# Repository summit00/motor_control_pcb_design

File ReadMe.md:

# STM32H563 BLDC Motor Controller

A three-phase BLDC/PMSM motor controller designed for high-performance Field-Oriented Control (FOC).

## Features

- STM32H563 microcontroller
- DRV8353 three-phase gate driver
- Three low-side current shunts
- Up to 60 V DC bus
- CAN interface
- USB-C interface
- Incremental encoder interface

## Repository Structure

```
.
├── motor_bldc_esc_V1.kicad_pro
├── motor_bldc_esc_V1.kicad_sch
├── motor_bldc_esc_V1.kicad_pcb
├── powerstage.kicad_sch
├── power.kicad_sch
├── mcu.kicad_sch
├── communication.kicad_sch
└── encoder.kicad_sch
```

## Status

🚧 Work in progress.

The hardware is currently under development and has not yet been validated on physical hardware.

## License

Hardware released under the CERN Open Hardware License.

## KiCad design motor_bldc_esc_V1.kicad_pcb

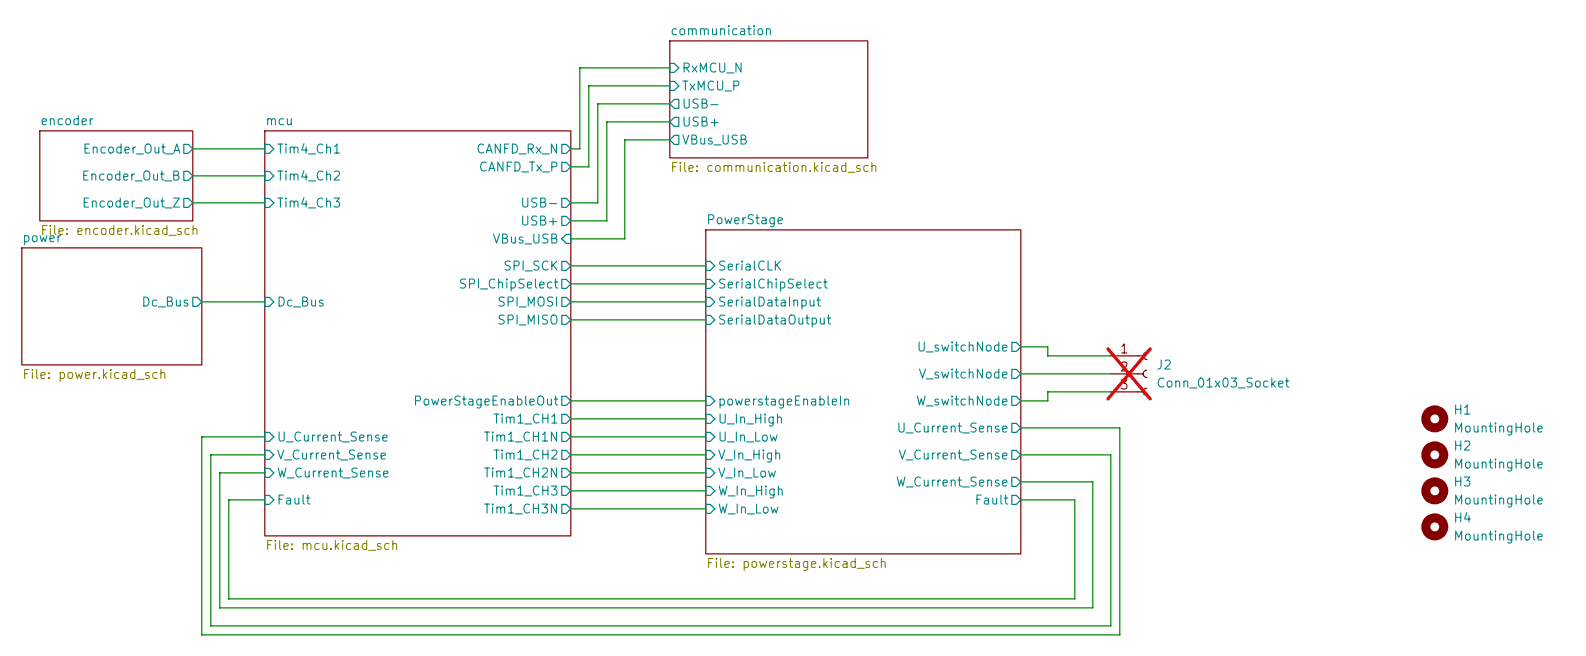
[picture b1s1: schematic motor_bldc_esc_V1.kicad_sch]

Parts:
H1, H2, H3, H4: MountingHole; MountingHole_3.2mm_M3
J2: Conn_01x03_Socket; SolderWire-4sqmm_1x03_P12mm_D3mm_OD6mm; not fitted

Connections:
/PowerStage/U_switchNode: J2.1; also elsewhere on the board
/PowerStage/V_switchNode: J2.2; also elsewhere on the board
/PowerStage/W_switchNode: J2.3; also elsewhere on the board

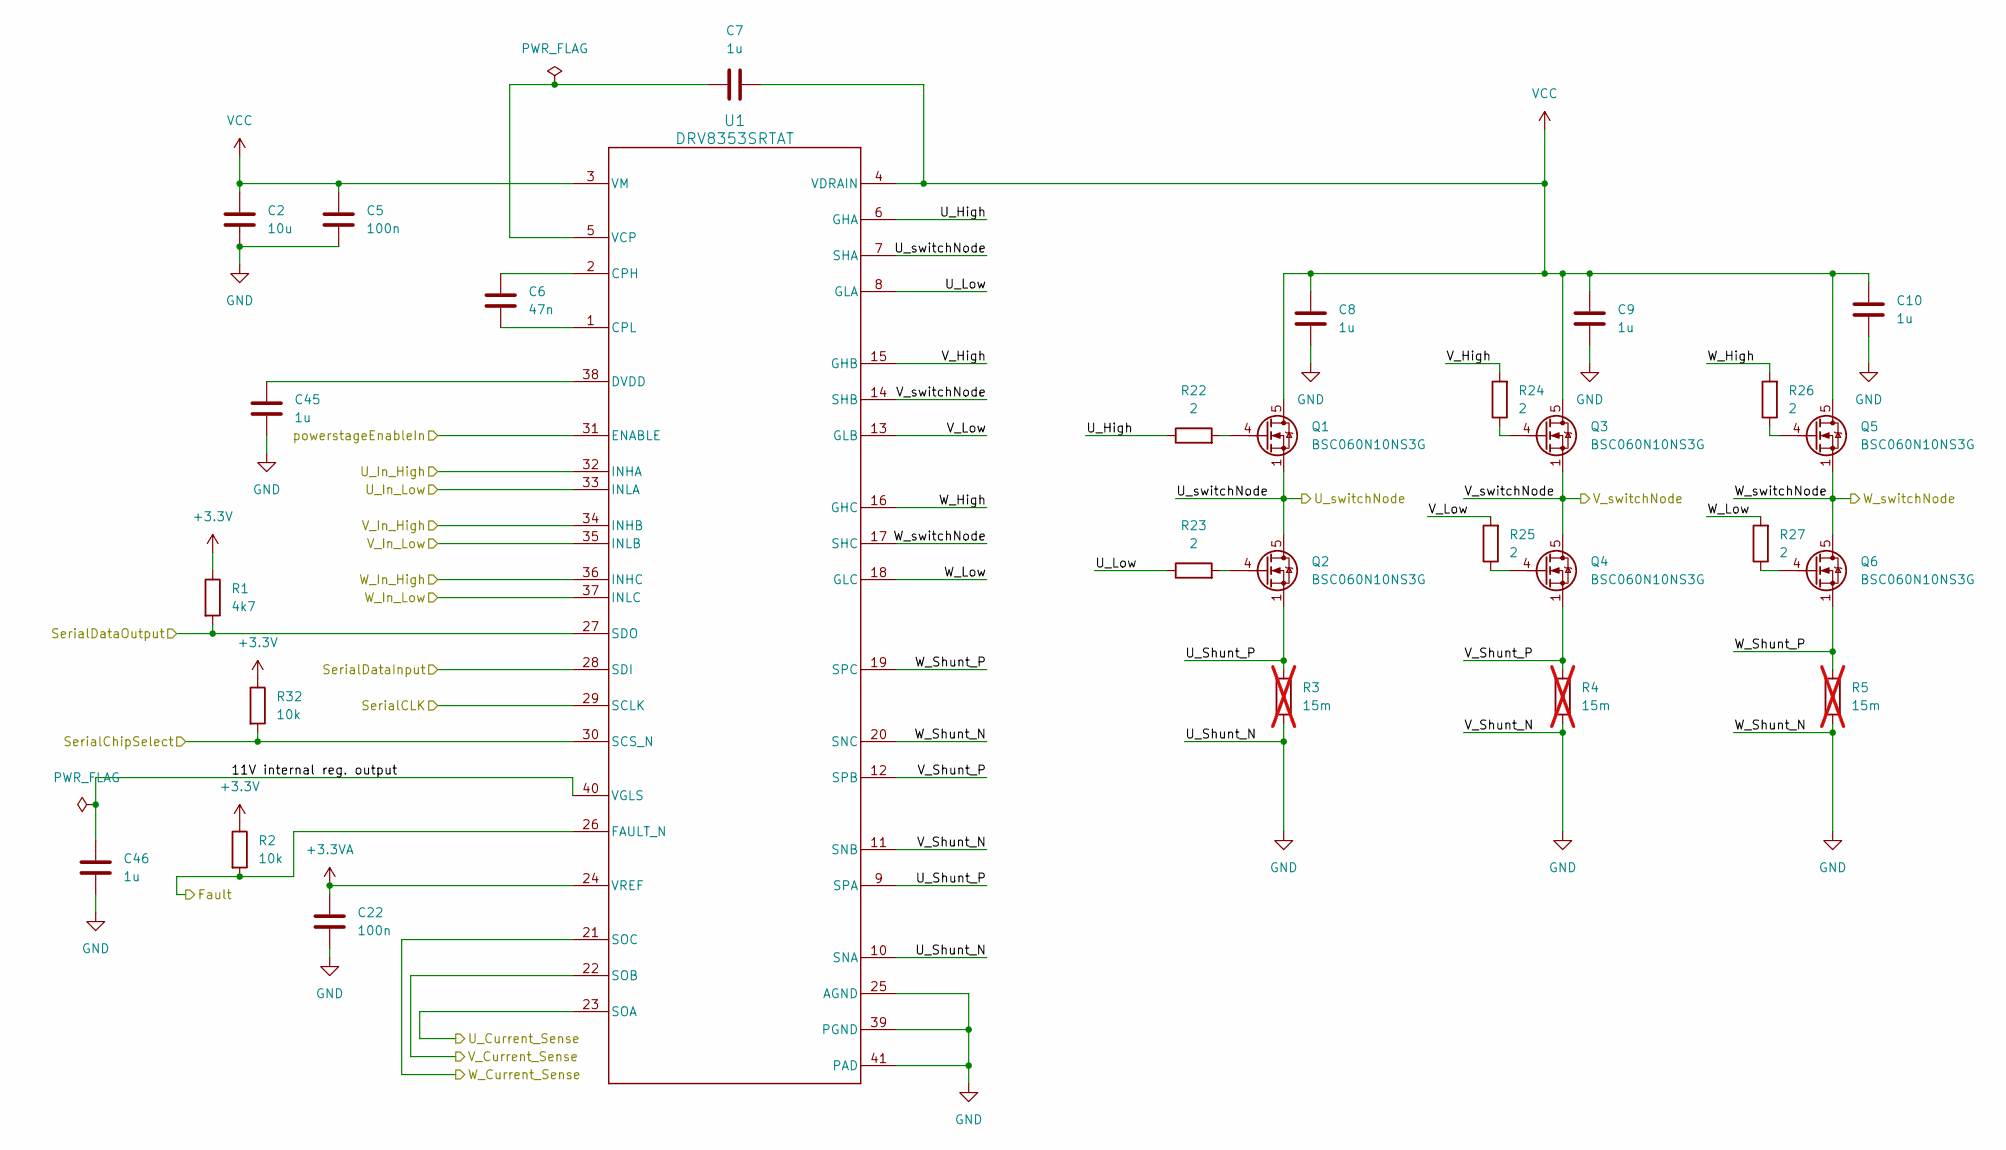
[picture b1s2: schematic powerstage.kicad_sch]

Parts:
C2: 10u; C_1210_3225Metric_Pad1.33x2.70mm_HandSolder; LCSC C5156756
C5: 100n; C_0805_2012Metric_Pad1.18x1.45mm_HandSolder; LCSC Part # C28233
C6: 47n; C_0805_2012Metric_Pad1.18x1.45mm_HandSolder; LCSC Part # C53134
C7: 1u; C_0805_2012Metric_Pad1.18x1.45mm_HandSolder; LCSC Part # C28323
C8, C9, C10: 1u; C_0805_2012Metric_Pad1.18x1.45mm_HandSolder; LCSC Part # C5370002
C22: 100n; C_0603_1608Metric; LCSC Part # C14663
C45, C46: 1u; C_0603_1608Metric; LCSC Part # C15849
Q1, Q2, Q3, Q4, Q5, Q6: BSC060N10NS3G; TDSON-8-1; LCSC Part # C501504
R1: 4k7; R_0603_1608Metric; LCSC Part # C23162
R2, R32: 10k; R_0805_2012Metric_Pad1.20x1.40mm_HandSolder; LCSC Part # C17414
R3, R4, R5: 15m; R_2512_6332Metric_Pad1.40x3.35mm_HandSolder; LCSC C7420045; not fitted
R22, R23, R24, R25, R26, R27: 2; R_0603_1608Metric; LCSC Part # C22977
U1: DRV8353SRTAT; LCSC Part # C2150480

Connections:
+3.3V: R1.1, R2.1, R32.1; also elsewhere on the board
+3.3VA: C22.1, U1.24 (VREF); also elsewhere on the board
/PowerStage/11V internal reg. output: C46.1, U1.40 (VGLS)
/PowerStage/Fault: R2.2, U1.26 (FAULT_N); also elsewhere on the board
/PowerStage/SerialCLK: U1.29 (SCLK); also elsewhere on the board
/PowerStage/SerialChipSelect: R32.2, U1.30 (SCS_N); also elsewhere on the board
/PowerStage/SerialDataInput: U1.28 (SDI); also elsewhere on the board
/PowerStage/SerialDataOutput: R1.2, U1.27 (SDO); also elsewhere on the board
/PowerStage/U_Current_Sense: U1.23 (SOA); also elsewhere on the board
/PowerStage/U_High: R22.1, U1.6 (GHA)
/PowerStage/U_In_High: U1.32 (INHA); also elsewhere on the board
/PowerStage/U_In_Low: U1.33 (INLA); also elsewhere on the board
/PowerStage/U_Low: R23.1, U1.8 (GLA)
/PowerStage/U_Shunt_P: Q2.1 (S), Q2.2 (S), Q2.3 (S), R3.1, U1.9 (SPA)
/PowerStage/U_switchNode: Q1.1 (S), Q1.2 (S), Q1.3 (S), Q2.5 (D), U1.7 (SHA); also elsewhere on the board
/PowerStage/V_Current_Sense: U1.22 (SOB); also elsewhere on the board
/PowerStage/V_High: R24.2, U1.15 (GHB)
/PowerStage/V_In_High: U1.34 (INHB); also elsewhere on the board
/PowerStage/V_In_Low: U1.35 (INLB); also elsewhere on the board
/PowerStage/V_Low: R25.2, U1.13 (GLB)
/PowerStage/V_Shunt_P: Q4.1 (S), Q4.2 (S), Q4.3 (S), R4.1, U1.12 (SPB)
/PowerStage/V_switchNode: Q3.1 (S), Q3.2 (S), Q3.3 (S), Q4.5 (D), U1.14 (SHB); also elsewhere on the board
/PowerStage/W_Current_Sense: U1.21 (SOC); also elsewhere on the board
/PowerStage/W_High: R26.2, U1.16 (GHC)
/PowerStage/W_In_High: U1.36 (INHC); also elsewhere on the board
/PowerStage/W_In_Low: U1.37 (INLC); also elsewhere on the board
/PowerStage/W_Low: R27.2, U1.18 (GLC)
/PowerStage/W_Shunt_P: Q6.1 (S), Q6.2 (S), Q6.3 (S), R5.1, U1.19 (SPC)
/PowerStage/W_switchNode: Q5.1 (S), Q5.2 (S), Q5.3 (S), Q6.5 (D), U1.17 (SHC); also elsewhere on the board
/PowerStage/powerstageEnableIn: U1.31 (ENABLE); also elsewhere on the board
GND: C2.2, C5.1, C8.2, C9.2, C10.2, C22.2, C45.2, C46.2, R3.2, R4.2, R5.2, U1.10 (SNA), U1.11 (SNB), U1.20 (SNC), U1.25 (AGND), U1.39 (PGND), U1.41 (PAD); also elsewhere on the board
unnamed: Q1.4 (G), R22.2
unnamed: Q2.4 (G), R23.2
unnamed: Q3.4 (G), R24.1
unnamed: Q4.4 (G), R25.1
unnamed: Q5.4 (G), R26.1
unnamed: Q6.4 (G), R27.1
unnamed: C6.2, U1.2 (CPH)
unnamed: C6.1, U1.1 (CPL)
unnamed: C45.1, U1.38 (DVDD)
unnamed: C7.1, U1.5 (VCP)
VCC: C2.1, C5.2, C7.2, C8.1, C9.1, C10.1, Q1.5 (D), Q3.5 (D), Q5.5 (D), U1.3 (VM), U1.4 (VDRAIN); also elsewhere on the board

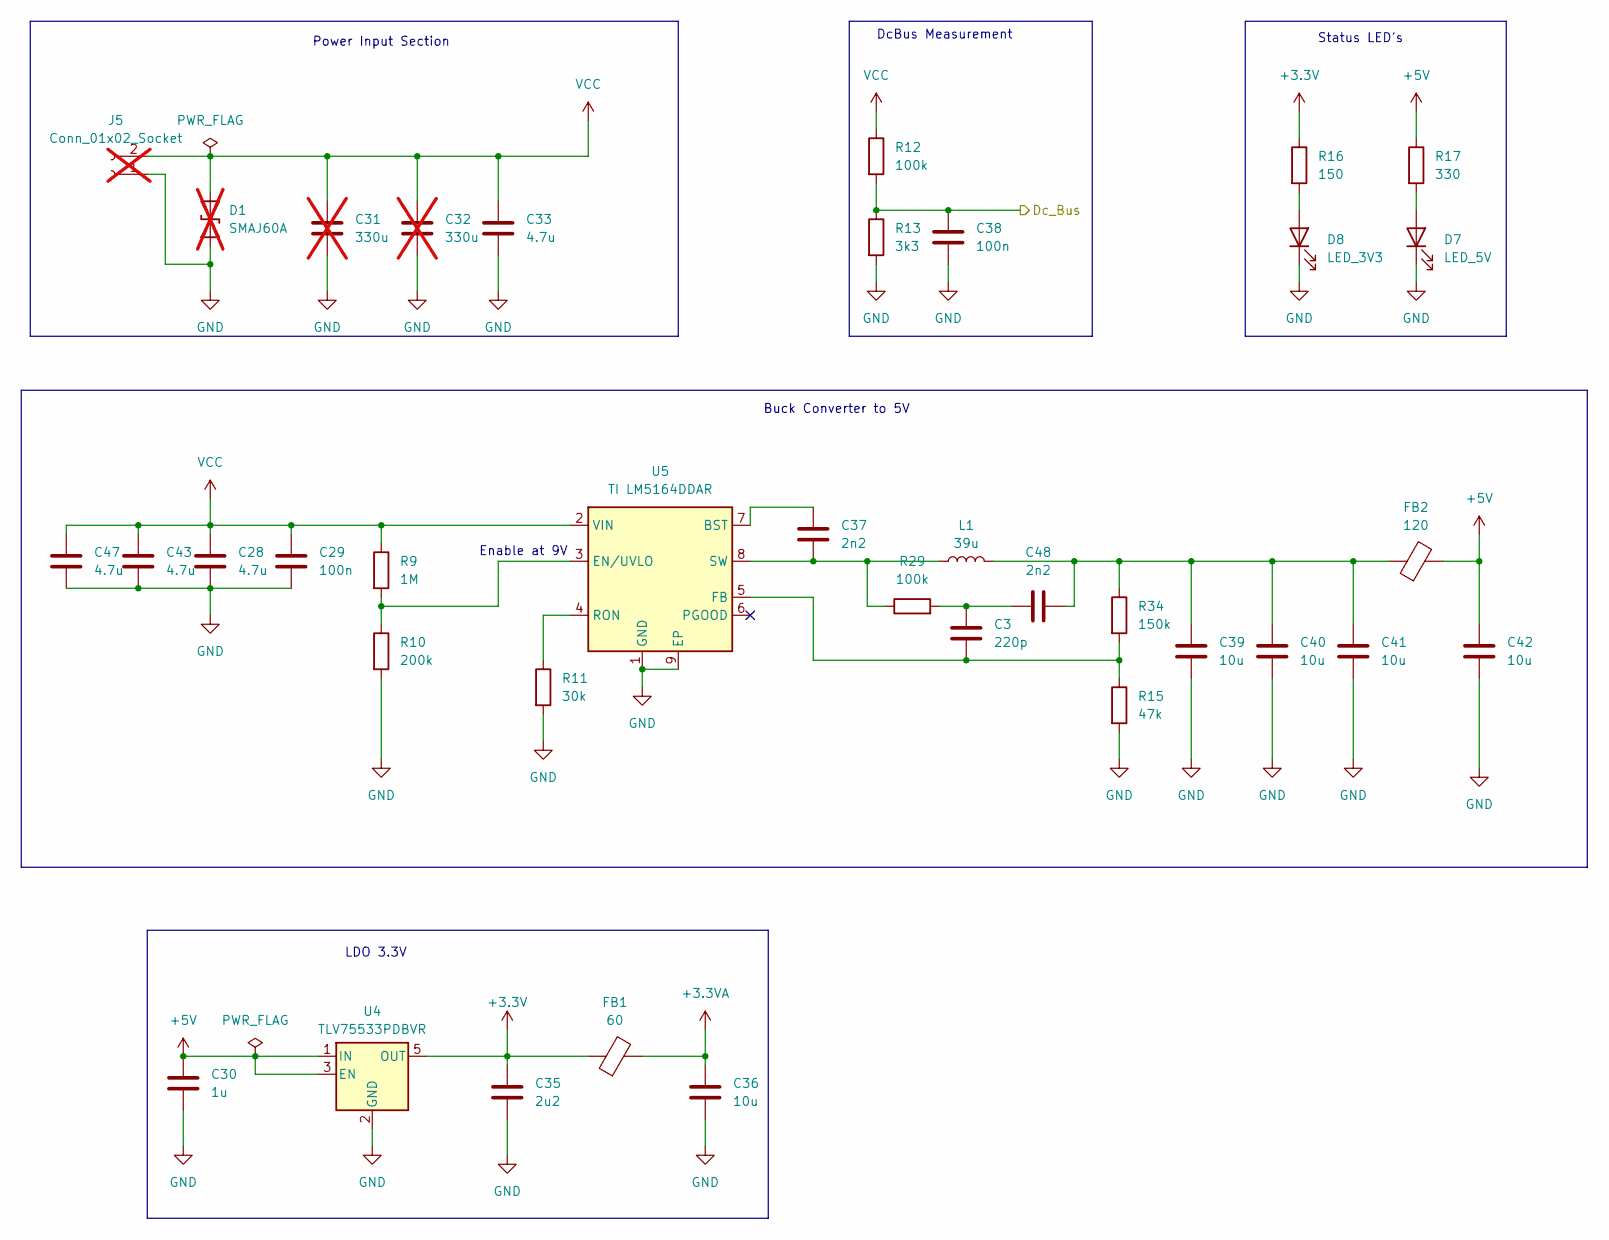
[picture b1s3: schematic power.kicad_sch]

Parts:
C3: 220p; C_0603_1608Metric; LCSC Part # C1603
C28, C33, C43, C47: 4.7u; C_1210_3225Metric_Pad1.33x2.70mm_HandSolder; LCSC C381466
C29, C38: 100n; C_0805_2012Metric_Pad1.18x1.45mm_HandSolder; LCSC Part # C28233
C30: 1u; C_0603_1608Metric; LCSC Part # C15849
C31, C32: 330u; 100ZLJ330M12.5X35; not fitted
C35: 2u2; C_0603_1608Metric; LCSC Part # C23630
C36, C39, C40, C41, C42: 10u; R_0805_2012Metric_Pad1.20x1.40mm_HandSolder; LCSC Part # C15850
C37, C48: 2n2; C_0603_1608Metric; LCSC Part # C1604
D1: SMAJ60A; D_SMA-SMB_Universal_Handsoldering; not fitted
D7: LED_5V; LED_0805_2012Metric; LCSC C84256
D8: LED_3V3; LED_0805_2012Metric; LCSC C84256
FB1: 60; L_0805_2012Metric_Pad1.05x1.20mm_HandSolder; LCSC Part # C845118
FB2: 120; L_0603_1608Metric_Pad1.05x0.95mm_HandSolder; LCSC Part # C14709
J5: Conn_01x02_Socket; SolderWire-4sqmm_1x02_P12mm_D3mm_OD6mm; not fitted
L1: 39u; L_Sunlord_SWPA8040S; LCSC Part # C206289
R9: 1M; R_0805_2012Metric; LCSC Part # C17514
R10: 200k; R_0805_2012Metric; LCSC Part # C17539
R11: 30k; R_0603_1608Metric; LCSC C22984
R12: 100k; R_0805_2012Metric_Pad1.20x1.40mm_HandSolder; LCSC Part # C149504
R13: 3k3; R_0805_2012Metric_Pad1.20x1.40mm_HandSolder; LCSC Part # C26010
R15: 47k; R_0603_1608Metric; LCSC Part # C25819
R16: 150; R_0805_2012Metric_Pad1.20x1.40mm_HandSolder; LCSC Part # C17471
R17: 330; R_0603_1608Metric; LCSC Part # C23138
R29: 100k; R_0603_1608Metric; LCSC Part # C25803
R34: 150k; R_0603_1608Metric; LCSC Part # C22807
U4: TLV75533PDBVR; SOT-23-5; LCSC Part # C404027
U5: TI LM5164DDAR; LM5164DDAR; LCSC Part # C477928

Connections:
+3.3V: C35.1, FB1.1, R16.1, U4.5 (OUT); also elsewhere on the board
+3.3VA: C36.1, FB1.2; also elsewhere on the board
+5V: C30.1, C42.1, FB2.2, R17.1, U4.1 (IN), U4.3 (EN); also elsewhere on the board
/mcu/Dc_Bus: C38.2, R12.2, R13.1; also elsewhere on the board
GND: C28.2, C29.1, C30.2, C31.2, C32.2, C33.2, C35.2, C36.2, C38.1, C39.2, C40.2, C41.2, C42.2, C43.2, C47.2, D1.1 (A1), D7.1 (K), D8.1 (K), J5.1, R10.2, R11.2, R13.2, R15.2, U4.2 (GND), U5.1 (GND), U5.9 (EP); also elsewhere on the board
unnamed: C3.1, C48.1, R29.2
unnamed: C39.1, C40.1, C41.1, C48.2, FB2.1, L1.2, R34.1
unnamed: D7.2 (A), R17.2
unnamed: D8.2 (A), R16.2
unnamed: C37.1, U5.7 (BST)
unnamed: R9.2, R10.1, U5.3 (EN/UVLO)
unnamed: C3.2, R15.1, R34.2, U5.5 (FB)
unnamed: R11.1, U5.4 (RON)
unnamed: C37.2, L1.1, R29.1, U5.8 (SW)
VCC: C28.1, C29.2, C31.1, C32.1, C33.1, C43.1, C47.1, D1.2 (A2), J5.2, R9.1, R12.1, U5.2 (VIN); also elsewhere on the board

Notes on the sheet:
Buck Converter to 5V
Enable at 9V
Power Input Section
LDO 3.3V
Status LED's
DcBus Measurement

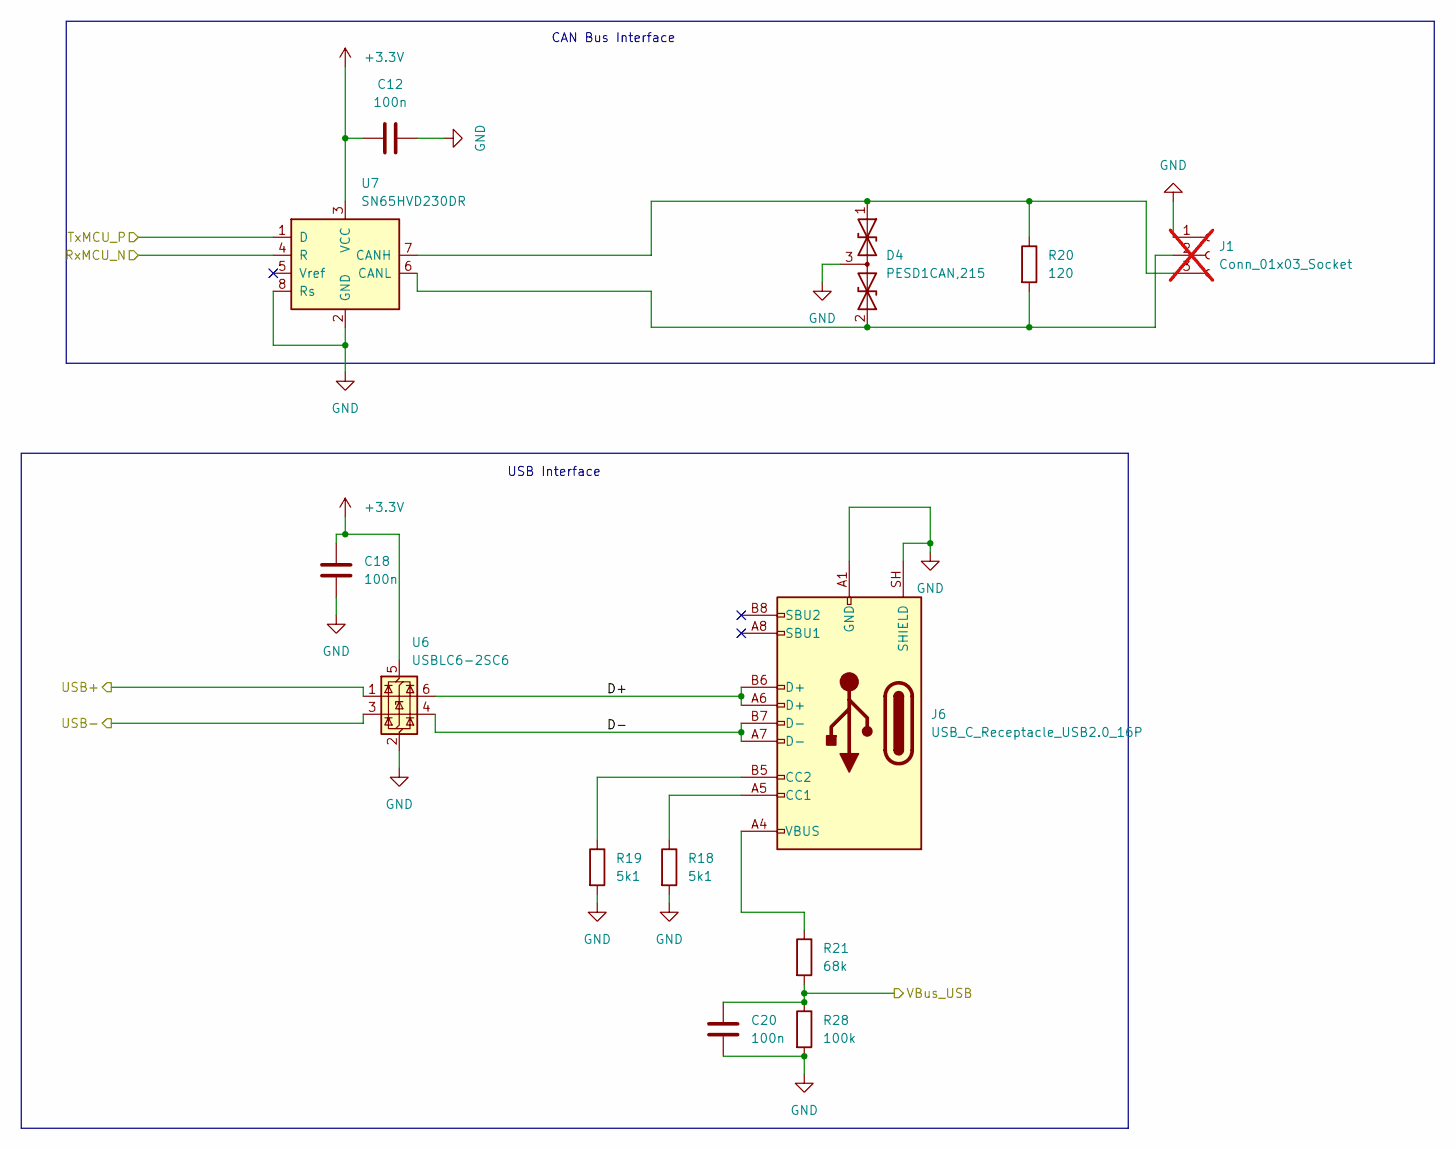
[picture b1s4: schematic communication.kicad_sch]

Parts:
C12, C18, C20: 100n; C_0603_1608Metric; LCSC Part # C14663
D4: PESD1CAN,215; SOT-23; LCSC Part # C15771
J1: Conn_01x03_Socket; JST_EH_B3B-EH-A_1x03_P2.50mm_Vertical; not fitted
J6: USB_C_Receptacle_USB2.0_16P; USB_C_Receptacle_G-Switch_GT-USB-7010ASV; LCSC Part # C2988369
R18, R19: 5k1; R_0603_1608Metric; LCSC Part # C23189
R20: 120; R_0603_1608Metric; LCSC Part # C22787
R21: 68k; R_0603_1608Metric; LCSC Part # C23231
R28: 100k; R_0603_1608Metric; LCSC Part # C25803
U6: USBLC6-2SC6; SOT-23-6; LCSC Part # C7519
U7: SN65HVD230DR; SOIC-8_3.9x4.9mm_P1.27mm; LCSC Part # C12084

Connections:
+3.3V: C12.1, C18.1, U6.5 (VBUS), U7.3 (VCC); also elsewhere on the board
/communication/D+: J6.A6 (D+), J6.B6 (D+), U6.6 (I/O1)
/communication/D-: J6.A7 (D-), J6.B7 (D-), U6.4 (I/O2)
/communication/RxMCU_N: U7.4 (R); also elsewhere on the board
/communication/TxMCU_P: U7.1 (D); also elsewhere on the board
/communication/USB+: U6.1 (I/O1); also elsewhere on the board
/communication/USB-: U6.3 (I/O2); also elsewhere on the board
/communication/VBus_USB: C20.1, R21.2, R28.1; also elsewhere on the board
GND: C12.2, C18.2, C20.2, D4.3 (common), J1.1, J6.A1 (GND), J6.A12 (GND), J6.B1 (GND), J6.B12 (GND), J6.SH (SHIELD), R18.2, R19.2, R28.2, U6.2 (GND), U7.2 (GND), U7.8 (Rs); also elsewhere on the board
unnamed: D4.1 (A1), J1.3, R20.1, U7.7 (CANH)
unnamed: D4.2 (A2), J1.2, R20.2, U7.6 (CANL)
unnamed: J6.A5 (CC1), R18.1
unnamed: J6.B5 (CC2), R19.1
unnamed: J6.A4 (VBUS), J6.A9 (VBUS), J6.B4 (VBUS), J6.B9 (VBUS), R21.1

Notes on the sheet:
CAN Bus Interface
USB Interface

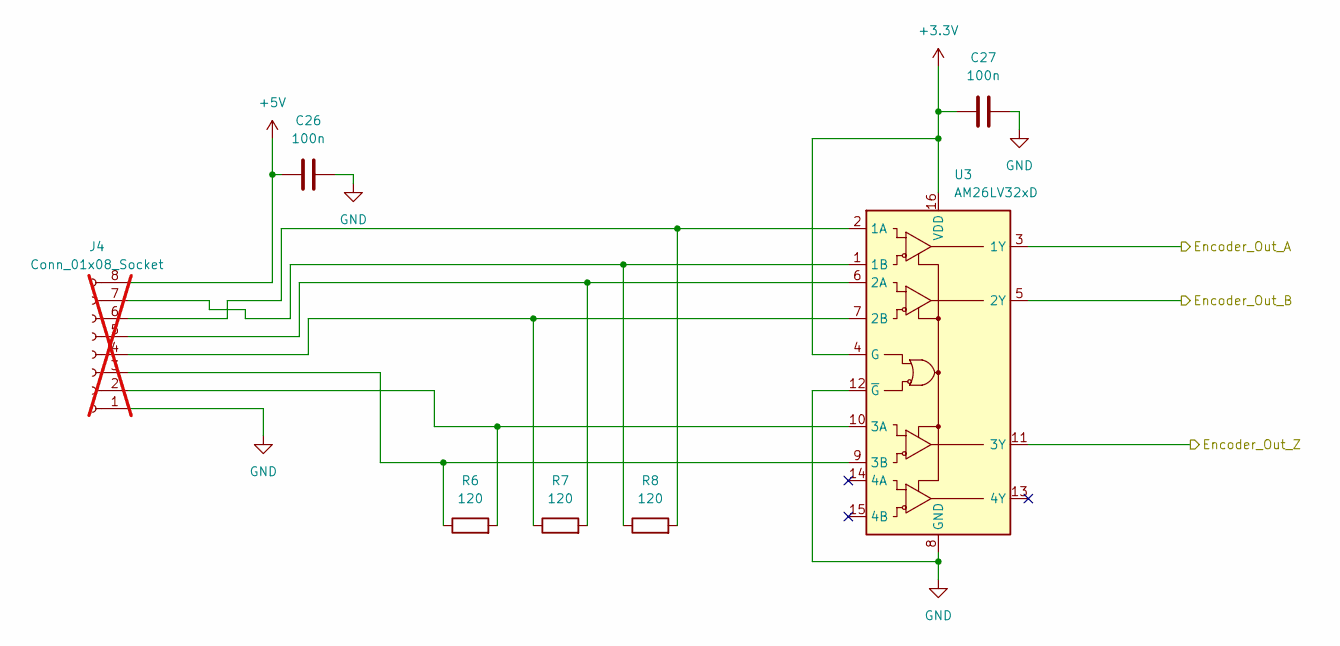
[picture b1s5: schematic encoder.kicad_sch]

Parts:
C26, C27: 100n; C_0805_2012Metric_Pad1.18x1.45mm_HandSolder; LCSC Part # C28233
J4: Conn_01x08_Socket; JST_XH_B8B-XH-A_1x08_P2.50mm_Vertical; not fitted
R6, R7, R8: 120; R_0805_2012Metric_Pad1.20x1.40mm_HandSolder; LCSC Part # C17437
U3: AM26LV32xD; SOIC-16_3.9x9.9mm_P1.27mm; LCSC Part # C527448

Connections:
+3.3V: C27.2, U3.4 (G), U3.16 (VDD); also elsewhere on the board
+5V: C26.2, J4.8; also elsewhere on the board
/encoder/Encoder_Out_A: U3.3 (1Y); also elsewhere on the board
/encoder/Encoder_Out_B: U3.5 (2Y); also elsewhere on the board
/encoder/Encoder_Out_Z: U3.11 (3Y); also elsewhere on the board
GND: C26.1, C27.1, J4.1, U3.8 (GND), U3.12 (~G); also elsewhere on the board
unnamed: J4.2, R6.2, U3.10 (3A)
unnamed: J4.3, R6.1, U3.9 (3B)
unnamed: J4.4, R7.1, U3.7 (2B)
unnamed: J4.5, R7.2, U3.6 (2A)
unnamed: J4.6, R8.2, U3.2 (1A)
unnamed: J4.7, R8.1, U3.1 (1B)

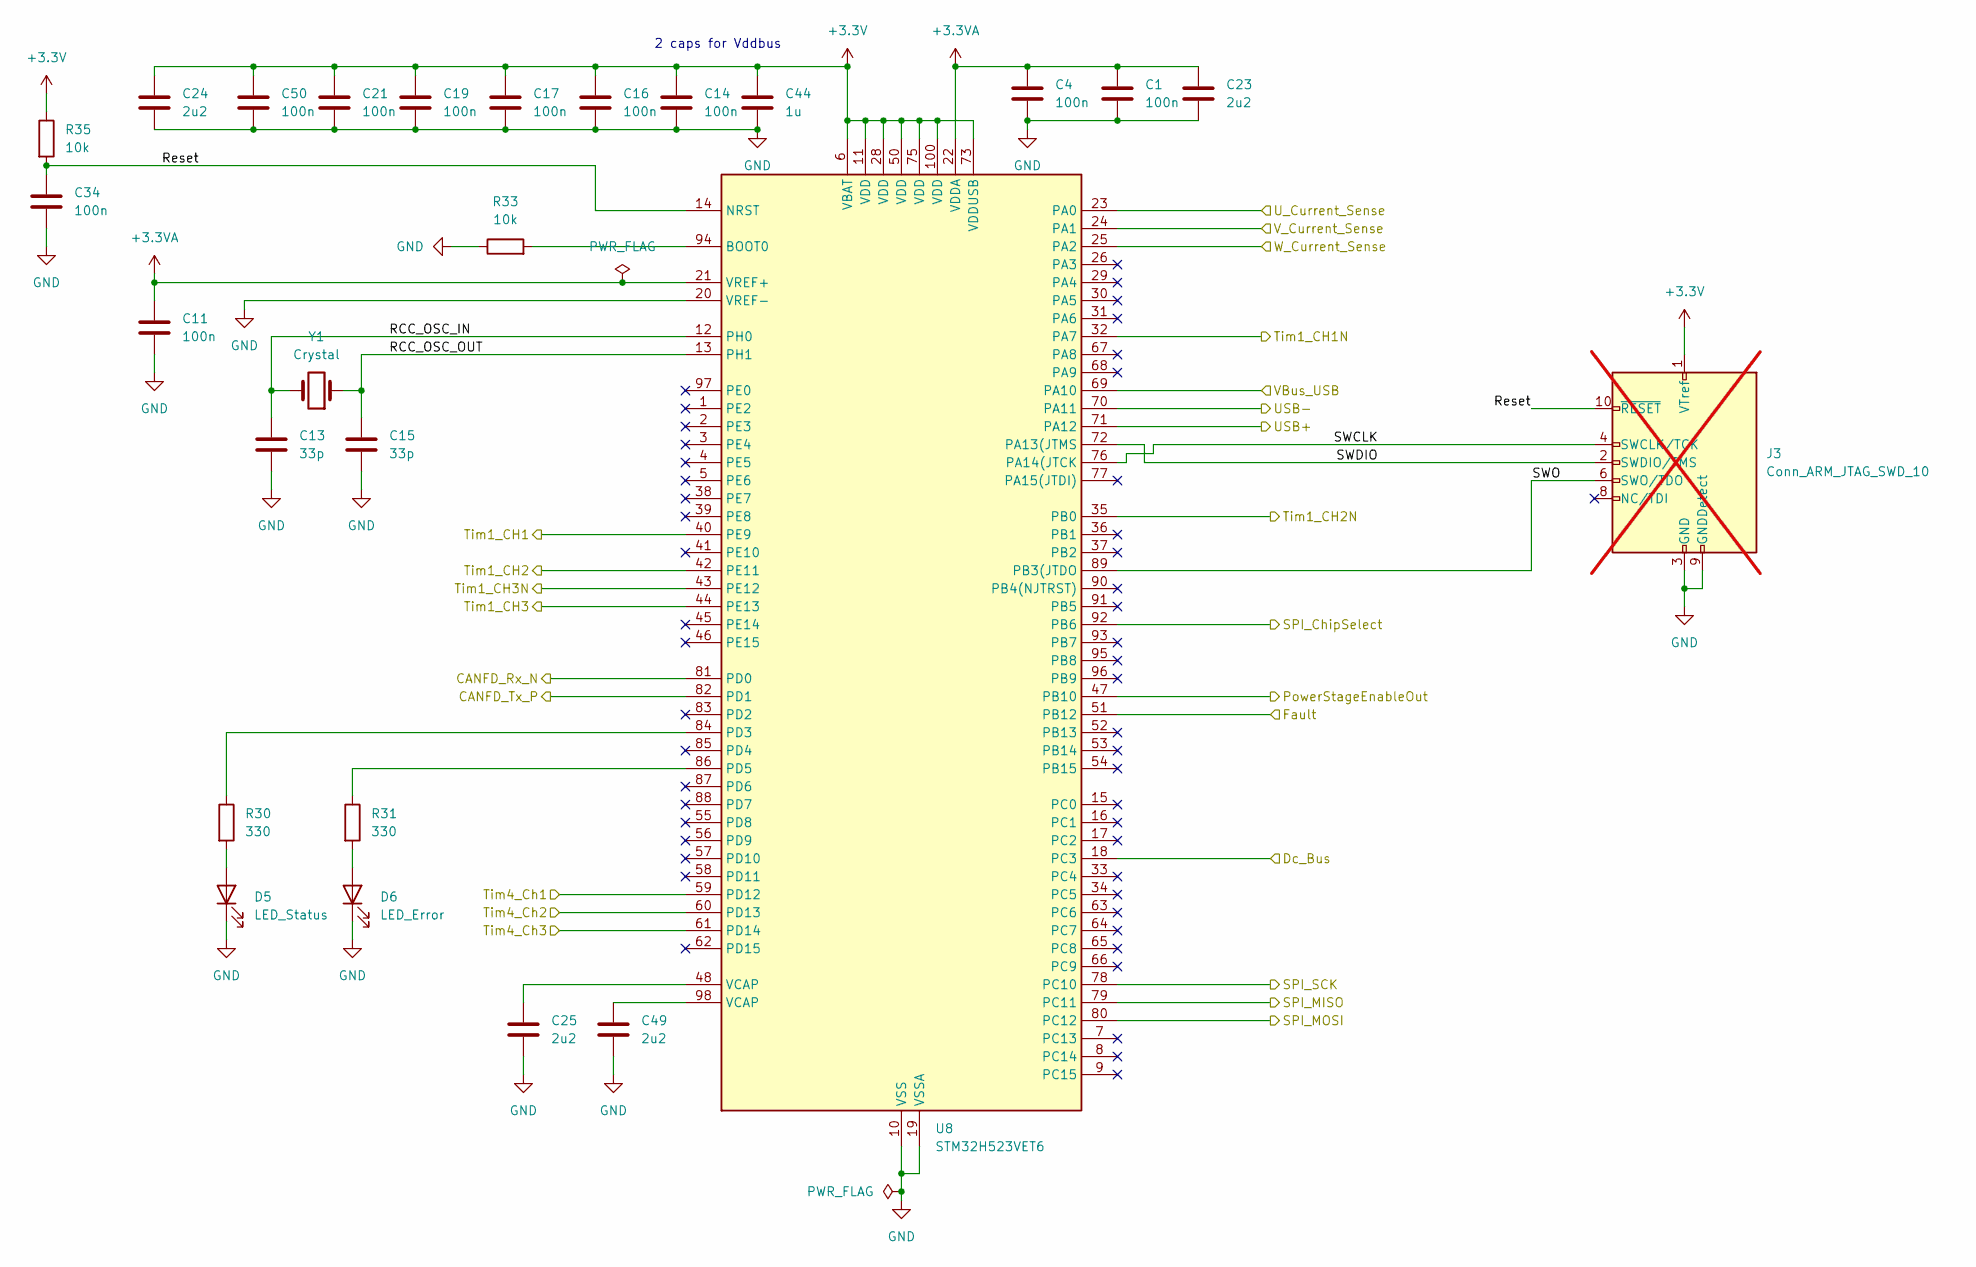
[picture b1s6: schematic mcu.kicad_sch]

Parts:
C1, C4, C11, C14, C16, C17, C19, C21, C34, C50: 100n; C_0603_1608Metric; LCSC Part # C14663
C13, C15: 33p; C_0603_1608Metric
C23, C24, C25, C49: 2u2; C_0603_1608Metric; LCSC Part # C23630
C44: 1u; C_0603_1608Metric; LCSC Part # C15849
D5: LED_Status; LED_0805_2012Metric; LCSC C84256
D6: LED_Error; LED_0805_2012Metric; LCSC C84256
J3: Conn_ARM_JTAG_SWD_10; PinHeader_2x05_P1.27mm_Vertical; not fitted
R30, R31: 330; R_0603_1608Metric; LCSC Part # C23138
R33, R35: 10k; R_0805_2012Metric_Pad1.20x1.40mm_HandSolder; LCSC Part # C17414
U8: STM32H523VET6; LQFP-100_14x14mm_P0.5mm; LCSC Part # C27338462
Y1: Crystal; Crystal_SMD_5032-2Pin_5.0x3.2mm_HandSoldering; LCSC Part # C115962

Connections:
+3.3V: C14.1, C16.1, C17.1, C19.1, C21.1, C24.1, C44.1, C50.1, J3.1 (VTref), R35.1, U8.6 (VBAT), U8.11 (VDD), U8.28 (VDD), U8.50 (VDD), U8.73 (VDDUSB), U8.75 (VDD), U8.100 (VDD); also elsewhere on the board
+3.3VA: C1.1, C4.1, C11.1, C23.1, U8.21 (VREF+), U8.22 (VDDA); also elsewhere on the board
/PowerStage/Fault: U8.51 (PB12); also elsewhere on the board
/PowerStage/SerialCLK: U8.78 (PC10); also elsewhere on the board
/PowerStage/SerialChipSelect: U8.92 (PB6); also elsewhere on the board
/PowerStage/SerialDataInput: U8.80 (PC12); also elsewhere on the board
/PowerStage/SerialDataOutput: U8.79 (PC11); also elsewhere on the board
/PowerStage/U_Current_Sense: U8.23 (PA0); also elsewhere on the board
/PowerStage/U_In_High: U8.40 (PE9); also elsewhere on the board
/PowerStage/U_In_Low: U8.32 (PA7); also elsewhere on the board
/PowerStage/V_Current_Sense: U8.24 (PA1); also elsewhere on the board
/PowerStage/V_In_High: U8.42 (PE11); also elsewhere on the board
/PowerStage/V_In_Low: U8.35 (PB0); also elsewhere on the board
/PowerStage/W_Current_Sense: U8.25 (PA2); also elsewhere on the board
/PowerStage/W_In_High: U8.44 (PE13); also elsewhere on the board
/PowerStage/W_In_Low: U8.43 (PE12); also elsewhere on the board
/PowerStage/powerstageEnableIn: U8.47 (PB10); also elsewhere on the board
/communication/RxMCU_N: U8.81 (PD0); also elsewhere on the board
/communication/TxMCU_P: U8.82 (PD1); also elsewhere on the board
/communication/USB+: U8.71 (PA12); also elsewhere on the board
/communication/USB-: U8.70 (PA11); also elsewhere on the board
/communication/VBus_USB: U8.69 (PA10); also elsewhere on the board
/encoder/Encoder_Out_A: U8.59 (PD12); also elsewhere on the board
/encoder/Encoder_Out_B: U8.60 (PD13); also elsewhere on the board
/encoder/Encoder_Out_Z: U8.61 (PD14); also elsewhere on the board
/mcu/Dc_Bus: U8.18 (PC3); also elsewhere on the board
/mcu/RCC_OSC_IN: C13.1, U8.12 (PH0), Y1.2
/mcu/RCC_OSC_OUT: C15.1, U8.13 (PH1), Y1.1
/mcu/Reset: C34.1, J3.10 (~RESET), R35.2, U8.14 (NRST)
/mcu/SWCLK: J3.4 (SWCLK/TCK), U8.76 (PA14(JTCK)
/mcu/SWDIO: J3.2 (SWDIO/TMS), U8.72 (PA13(JTMS)
/mcu/SWO: J3.6 (SWO/TDO), U8.89 (PB3(JTDO)
GND: C1.2, C4.2, C11.2, C13.2, C14.2, C15.2, C16.2, C17.2, C19.2, C21.2, C23.2, C24.2, C25.2, C34.2, C44.2, C49.2, C50.2, D5.1 (K), D6.1 (K), J3.3 (GND), J3.5 (GND), J3.9 (GNDDetect), R33.1, U8.10 (VSS), U8.19 (VSSA), U8.20 (VREF-), U8.27 (VSS), U8.49 (VSS), U8.74 (VSS), U8.99 (VSS); also elsewhere on the board
unnamed: C25.1, U8.48 (VCAP)
unnamed: C49.1, U8.98 (VCAP)
unnamed: D5.2 (A), R30.2
unnamed: D6.2 (A), R31.2
unnamed: R33.2, U8.94 (BOOT0)
unnamed: R30.1, U8.84 (PD3)
unnamed: R31.1, U8.86 (PD5)

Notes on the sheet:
2 caps for Vddbus

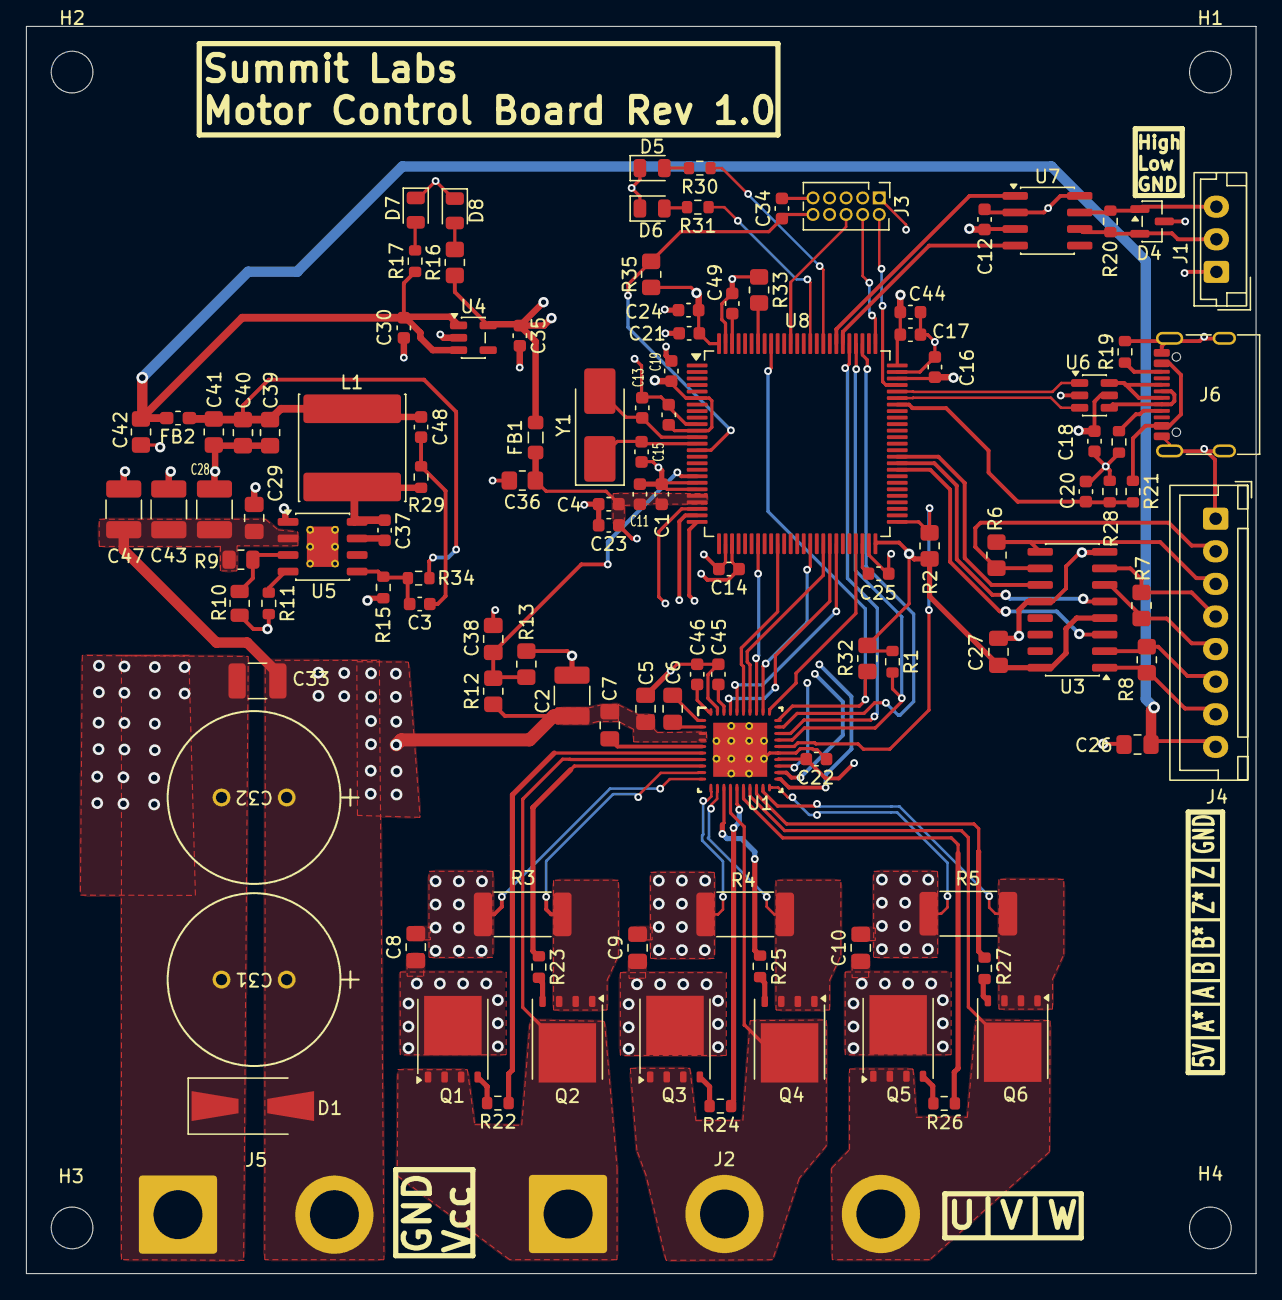
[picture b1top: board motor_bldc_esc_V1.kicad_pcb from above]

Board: 4 copper layers, 94.3 x 95.7 mm, 117 parts (0 on the bottom side), 87 nets.

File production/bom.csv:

Designator,Footprint,Quantity,Value,LCSC Part #
"C1, C11, C12, C14, C16, C17, C18, C19, C20, C21, C22, C34, C4, C50",0603,14,100n,C14663
"C10, C8, C9",0805,3,1u,C5370002
"C13, C15",0603,2,33p,https://jlcpcb.com/partdetail/2015-CL10C330JB8NNNC/C1663
C2,1210,1,10u,C5156756
"C23, C24, C25, C35, C49",0603,5,2u2,C23630
"C26, C27, C29, C38, C5",0805,5,100n,C28233
"C28, C33, C43, C47",1210,4,4.7u,C381466
C3,0603,1,220p,C1603
"C30, C44, C45, C46",0603,4,1u,C15849
"C36, C39, C40, C41, C42",0805,5,10u,C15850
"C37, C48",0603,2,2n2,C1604
C6,0805,1,47n,C53134
C7,0805,1,1u,C28323
D4,SOT-23,1,"PESD1CAN,215",C15771
D5,0805,1,LED_Status,C84256
D6,0805,1,LED_Error,C84256
D7,0805,1,LED_5V,C84256
D8,0805,1,LED_3V3,C84256
FB1,0805,1,60,C845118
FB2,0603,1,120,C14709
J6,USB_C_Receptacle_G-Switch_GT-USB-7010ASV,1,USB_C_Receptacle_USB2.0_16P,C2988369
L1,L_Sunlord_SWPA8040S,1,39u,C206289
"Q1, Q2, Q3, Q4, Q5, Q6",TDSON-8-1,6,BSC060N10NS3G,C501504
R1,0603,1,4k7,C23162
R10,0805,1,200k,C17539
R11,0603,1,30k,C22984
R12,0805,1,100k,C149504
R13,0805,1,3k3,C26010
R15,0603,1,47k,C25819
R16,0805,1,150,C17471
"R17, R30, R31",0603,3,330,C23138
"R18, R19",0603,2,5k1,C23189
"R2, R32, R33, R35",0805,4,10k,C17414
R20,0603,1,120,C22787
R21,0603,1,68k,C23231
"R22, R23, R24, R25, R26, R27",0603,6,2,C22977
"R28, R29",0603,2,100k,C25803
R34,0603,1,150k,C22807
"R6, R7, R8",0805,3,120,C17437
R9,0805,1,1M,C17514
U1,DRV8353SRTAT,1,DRV8353SRTAT,C2150480
U3,SOIC-16_3.9x9.9mm_P1.27mm,1,AM26LV32xD,C527448
U4,SOT-23-5,1,TLV75533PDBVR,C404027
U5,LM5164DDAR,1,TI LM5164DDAR,C477928
U6,SOT-23-6,1,USBLC6-2SC6,C7519
U7,SOIC-8_3.9x4.9mm_P1.27mm,1,SN65HVD230DR,C12084
U8,LQFP-100_14x14mm_P0.5mm,1,STM32H523VET6,C27338462
Y1,Crystal_SMD_5032-2Pin_5.0x3.2mm_HandSoldering,1,Crystal,C115962
